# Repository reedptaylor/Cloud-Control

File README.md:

# Cloud-Control
Senior Capstone Project

## Abstract
Communicating with groups of people during an emergency situation is an extremely important and challenging task. The Cloud Control project aims to create a crowd control solution using a hexacopter drone. The project consists of a ground control application (GCS) which records the user and transmits their voice data to the drone. The drone is equipped with our custom chip and a speaker system which will amplify the voice messages to a target on the ground. The target application is to be able to fly the drone over a single person or a group of people and relay a message to them from the GCS through a microphone. The GCS sends the captured voice data to the chip on the drone over a wireless connection, and the chip processes the data and outputs it through the attached speaker. The potential applications of this project are very broad and include search and rescue operations, active shooter scenarios, and even recreational events like concerts and festivals.

## Devices
1. Raspberry Pi acts as the GCS. Sends data over NRF24 wireless module.
2. LPC 4088 acts as reciever and is connected to drone. Recieves data over NRF24 wireless module.
3. Android device can serve as remote to the GCS to control it and send audio (through a TCP connection to the GCS).

## Prerequisites
1. Install pyaudio on Raspberry Pi
2. Turn on SPI controls and install spidev on Raspberry Pi
3. Configure USB microphone thorugh `/etc/asound.conf` on Raspberry Pi

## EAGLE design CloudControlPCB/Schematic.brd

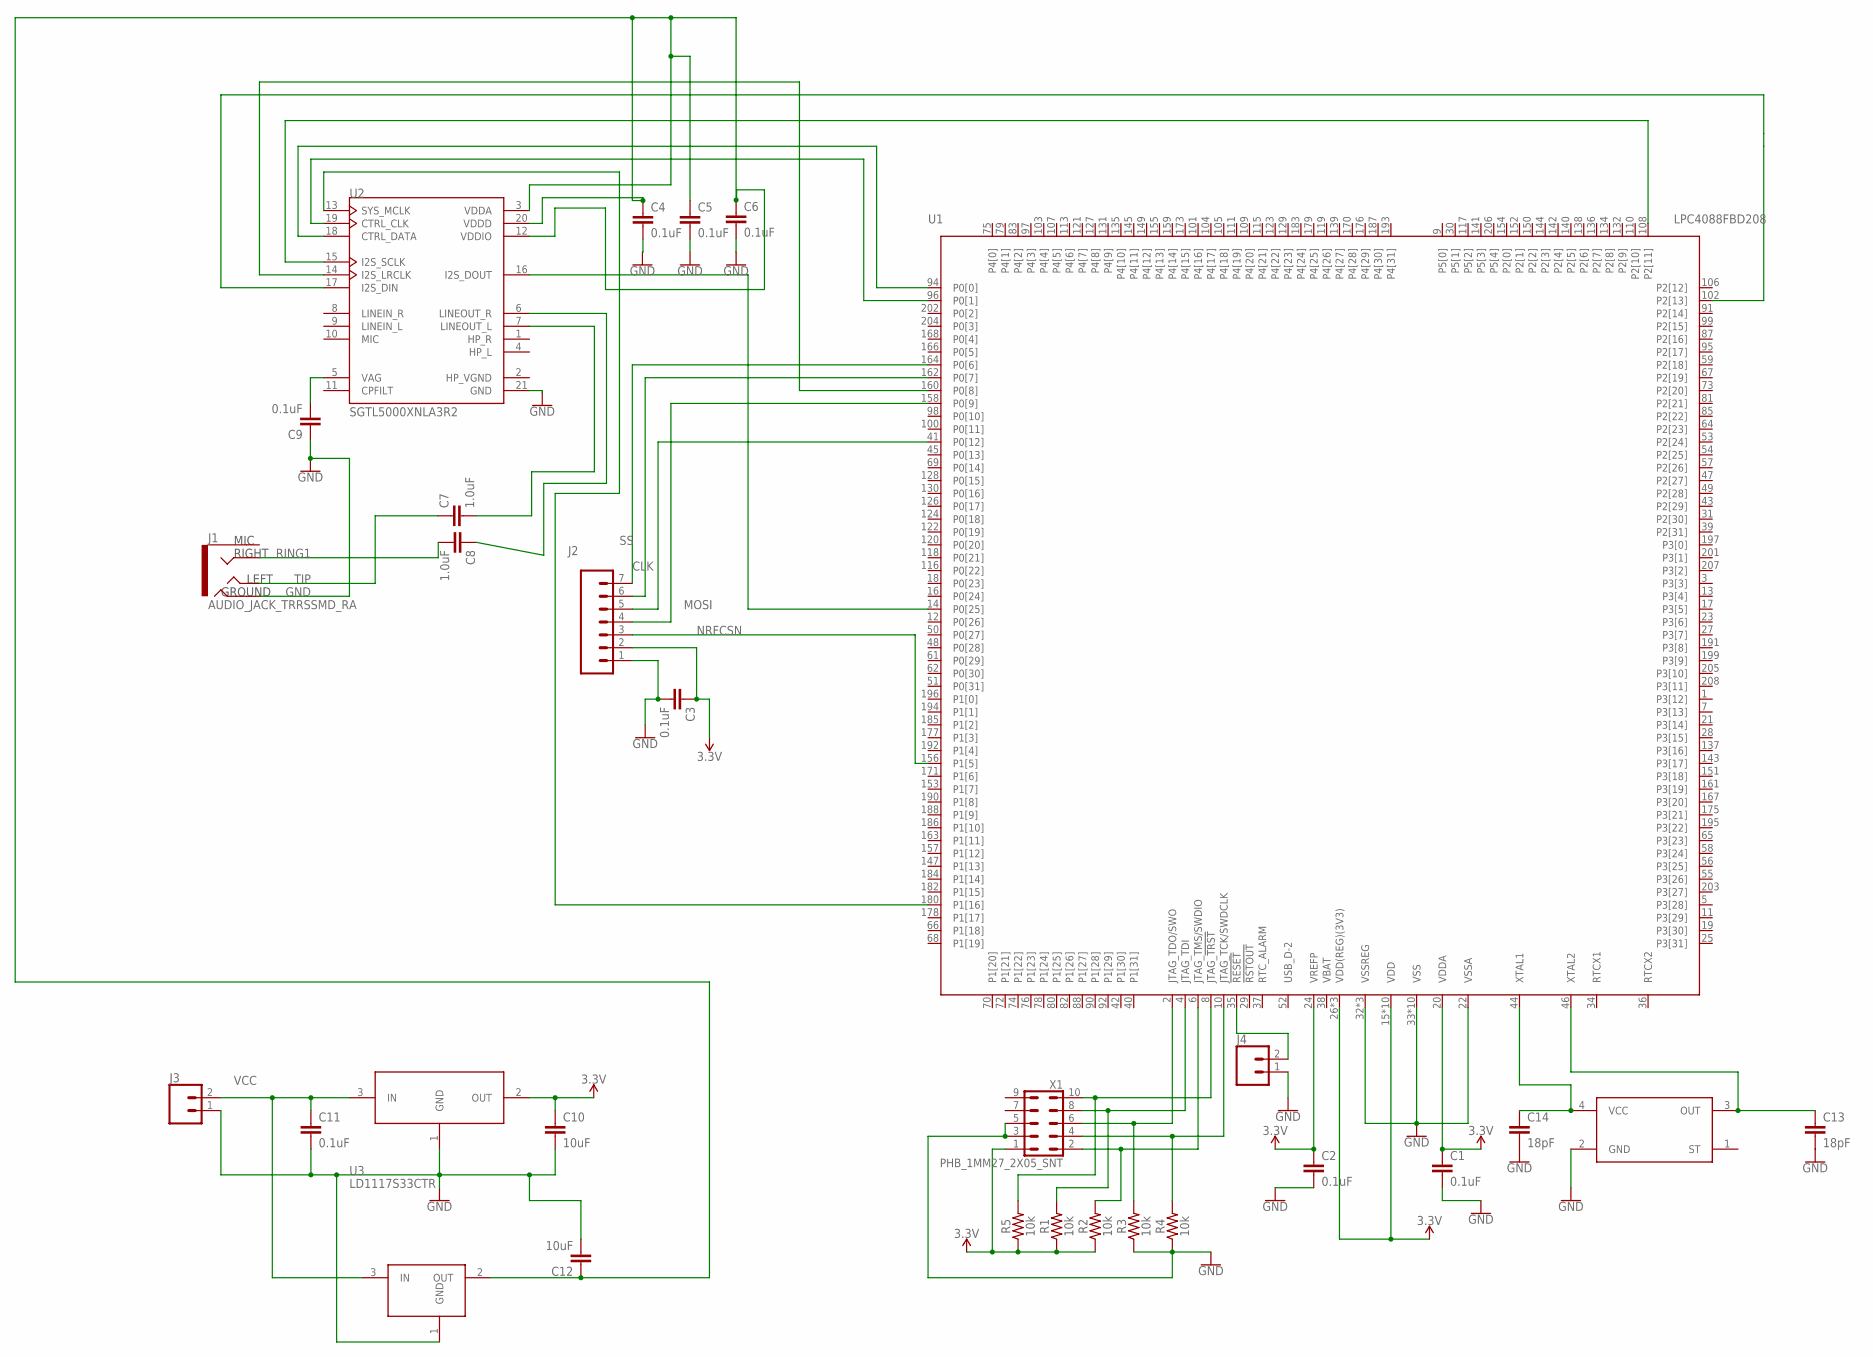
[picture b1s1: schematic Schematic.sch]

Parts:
C1, C2, C3, C11: 0.1uF; 0603
C4, C5, C6, C9: 0.1uF; 0402
C7, C8: 1.0uF; 0402
C10, C12: 10uF; 0603
C13, C14: 18pF; 0603
J1: AUDIO_JACK_TRRSSMD_RA; AUDIO_JACK_3.5MM_TRRS_SMD_RA
J2: CONN_07; 1X07
J3, J4: CONN_02; 1X02
R1, R2, R3, R4, R5: 10k; 0603
U1: LPC4088FBD208; SOT459-1
U2: SGTL5000XNLA3R2; QFN40P300X300X60-21N
U3: LD1117S33CTR; SOT223
U$1: SOT230P700X180-4N
U$2: XTAL_FA-238_25.0000MB-C3
X1: PHB_1MM27_2X05_SNT

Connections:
3.3V: C1.1, C2.1, C3.1, C10.1, J2.2, R1.1, R2.1, R5.1, U1.15 (VDD), U1.20 (VDDA), U1.24 (VREFP), U1.26 (VDD(REG)(3V3)), U1.60 (VDD), U1.71 (VDD), U1.86 (VDD(REG)(3V3)), U1.89 (VDD), U1.112 (VDD), U1.125 (VDD), U1.146 (VDD), U1.165 (VDD), U1.174 (VDD(REG)(3V3)), U1.181 (VDD), U1.198 (VDD), U3.2 (OUT), X1.1
CLK: J2.6, U1.162 (P0[7])
GND: C1.2, C2.2, C3.2, C4.2, C5.2, C6.2, C9.1, C10.2, C11.2, C12.2, C13.2, C14.2, J1.RING2, J2.1, J3.1, J4.1, R3.1, R4.1, U1.22 (VSSA), U1.32 (VSSREG), U1.33 (VSS), U1.63 (VSS), U1.77 (VSS), U1.84 (VSSREG), U1.93 (VSS), U1.114 (VSS), U1.133 (VSS), U1.148 (VSS), U1.169 (VSS), U1.172 (VSSREG), U1.189 (VSS), U1.200 (VSS), U2.21 (GND), U3.1 (GND), U$1.1 (GND), U$2.2 (GND), X1.3, X1.5; also elsewhere on the board
HP_VGND: U2.2 (HP_VGND)
MOSI: J2.4, U1.158 (P0[9])
unnamed: C8.1, U2.6 (LINEOUT_R)
unnamed: C7.2, U2.7 (LINEOUT_L)
unnamed: C14.1, U1.44 (XTAL1), U$2.4 (VCC)
unnamed: U1.14 (P0[25]), U2.16 (I2S_DOUT)
unnamed: U1.102 (P2[13]), U2.17 (I2S_DIN)
unnamed: U1.94 (P0[0]), U2.18 (CTRL_DATA)
unnamed: U1.96 (P0[1]), U2.19 (CTRL_CLK)
unnamed: U1.180 (P1[16]), U2.13 (SYS_MCLK)
unnamed: R3.2, U1.2 (JTAG_TDO/SWO), X1.6
unnamed: U1.108 (P2[11]), U2.15 (I2S_SCLK)
unnamed: U1.160 (P0[8]), U2.14 (I2S_LRCLK)
unnamed: R1.2, U1.4 (JTAG_TDI), X1.8
unnamed: R2.2, U1.6 (JTAG_TMS/SWDIO), X1.2
unnamed: R4.2, U1.10 (JTAG_TCK/SWDCLK), X1.4
unnamed: C9.2, U2.5 (VAG)
unnamed: R5.2, U1.8 (JTAG_!TRST), X1.10
unnamed: J2.5, U1.41 (P0[12])
unnamed: J4.2, U1.35 (!RESET!)
unnamed: C13.1, U1.46 (XTAL2), U$2.3 (OUT)
unnamed: C4.1, C5.1, C6.1, C12.1, U2.3 (VDDA), U2.12 (VDDIO), U2.20 (VDDD), U$1.2 (OUT)
NRFCSN: J2.3, U1.156 (P1[5])
RING1: C8.2, J1.RING1
SS: J2.7, U1.164 (P0[6])
TIP: C7.1, J1.TIP
VBAT: U1.38 (VBAT)
VCC: C11.1, J3.2, U3.3 (IN), U$1.3 (IN); also elsewhere on the board

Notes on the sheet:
MIC
RIGHT
LEFT
GROUND

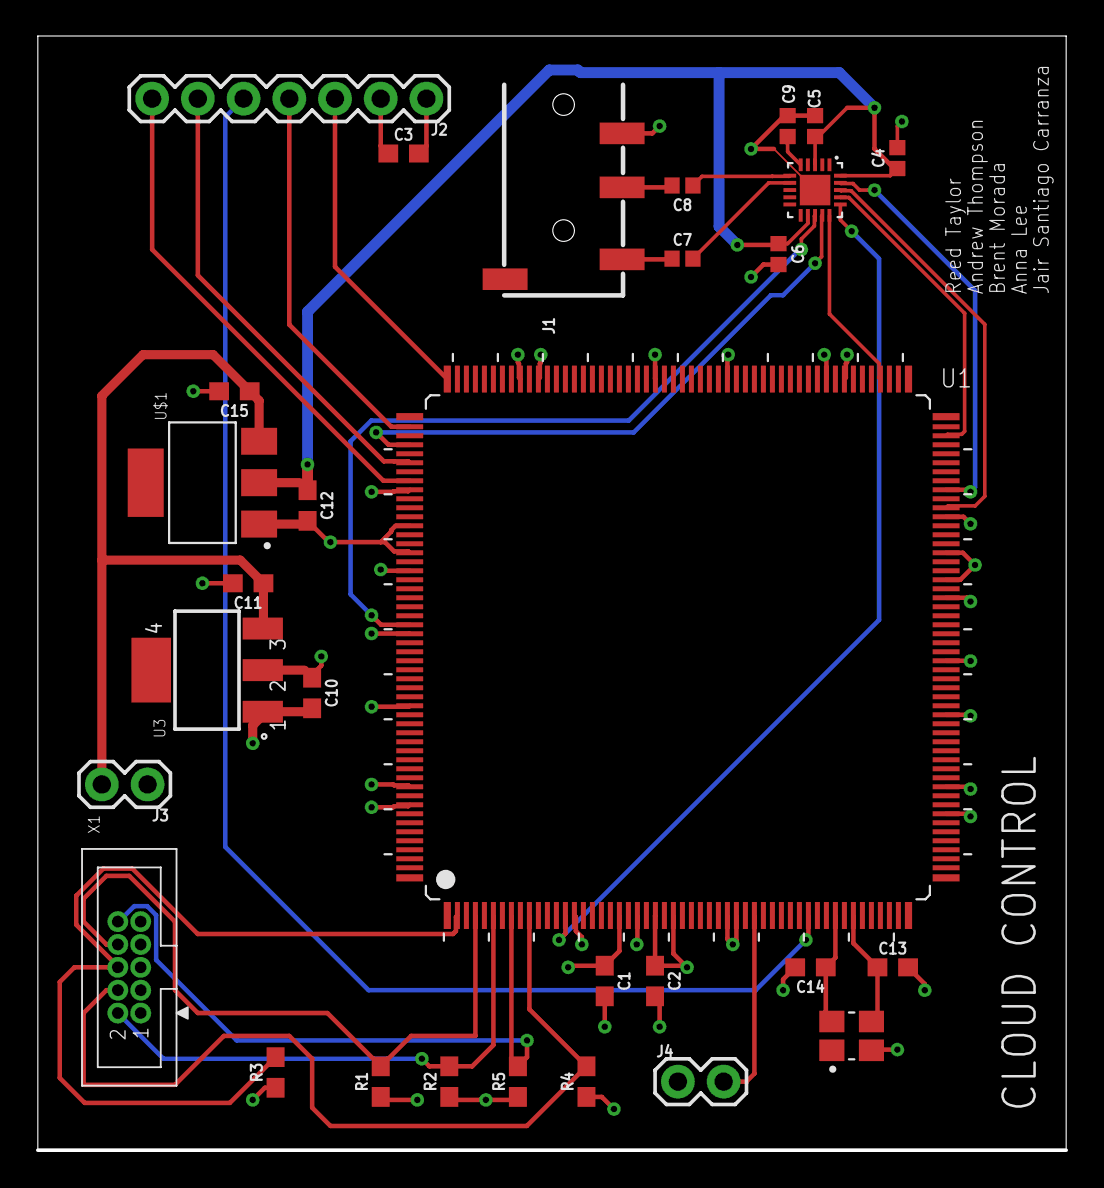
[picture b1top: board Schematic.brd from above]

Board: 4 copper layers, 57.1 x 61.9 mm, 30 parts (0 on the bottom side), 29 nets.

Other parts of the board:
C15: 0.1uF; 0603

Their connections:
GND: C15.2; also elsewhere on the board
VCC: C15.1; also elsewhere on the board

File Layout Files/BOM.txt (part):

Partlist exported from /Users/reed/Desktop/Cloud-Control/CloudControlPCB/Schematic.sch at 12/12/18 3:36 PM

Part Value                    Device                    Package                      Description                                                                                                     AVAILABILITY DESCRIPTION                                                                                   MF                 MP              PACKAGE                        PRICE PROD_ID    SF_ID     VALUE
C1   0.1uF                    0.1UF-0603-25V-(+80/-20%) 0603                         0.1µF ceramic capacitors                                                                                                                                                                                                                                                                           CAP-00810            0.1uF
C2   0.1uF                    0.1UF-0603-25V-(+80/-20%) 0603                         0.1µF ceramic capacitors                                                                                                                                                                                                                                                                           CAP-00810            0.1uF
C3   0.1uF                    0.1UF-0603-25V-(+80/-20%) 0603                         0.1µF ceramic capacitors                                                                                                                                                                                                                                                                           CAP-00810            0.1uF
C4   0.1uF                    0.1UF-0402-16V-10%        0402                         0.1µF ceramic capacitors                                                                                                                                                                                                                                                                           CAP-12416            0.1uF
C5   0.1uF                    0.1UF-0402-16V-10%        0402                         0.1µF ceramic capacitors                                                                                                                                                                                                                                                                           CAP-12416            0.1uF
C6   0.1uF                    0.1UF-0402-16V-10%        0402                         0.1µF ceramic capacitors                                                                                                                                                                                                                                                                           CAP-12416            0.1uF
C7   1.0uF                    1.0UF-0402-16V-10%        0402                         1µF ceramic capacitors                                                                                                                                                                                                                                                                             CAP-12417            1.0uF
C8   1.0uF                    1.0UF-0402-16V-10%        0402                         1µF ceramic capacitors                                                                                                                                                                                                                                                                             CAP-12417            1.0uF
C9   0.1uF                    0.1UF-0402-16V-10%        0402                         0.1µF ceramic capacitors                                                                                                                                                                                                                                                                           CAP-12416            0.1uF
C10  10uF                     10UF-0603-6.3V-20%        0603                         10.0µF ceramic capacitors                                                                                                                                                                                                                                                                          CAP-11015            10uF 
C11  0.1uF                    0.1UF-0603-25V-(+80/-20%) 0603                         0.1µF ceramic capacitors                                                                                                                                                                                                                                                                           CAP-00810            0.1uF
C12  10uF                     10UF-0603-6.3V-20%        0603                         10.0µF ceramic capacitors                                                                                                                                                                                                                                                                          CAP-11015            10uF 
C13  18pF                     18PF-0603-50V-5%          0603                         18pF ceramic capacitors                                                                                                                                                                                                                                                                            CAP-08267            18pF 
C14  18pF                     18PF-0603-50V-5%          0603                         18pF ceramic capacitors                                                                                                                                                                                                                                                                            CAP-08267            18pF 
C15  0.1uF                    0.1UF-0603-25V-(+80/-20%) 0603                         0.1µF ceramic capacitors                                                                                                                                                                                                                                                                           CAP-00810            0.1uF
J1   AUDIO_JACK_TRRSSMD_RA    AUDIO_JACK_TRRSSMD_RA     AUDIO_JACK_3.5MM_TRRS_SMD_RA Audio Jack - 3.5mm TRRS (SMD)                                                                                                                                                                                                                                                                      CONN-10676 PRT-12639      
J2                            CONN_07                   1X07                         Multi connection point. Often used as Generic Header-pin footprint for 0.1 inch spaced/style header connections                                                                                                                                                                                                              
J3                            CONN_02                   1X02                         Multi connection point. Often used as Generic Header-pin footprint for 0.1 inch spaced/style header connections                                                                                                                                                                                                              
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
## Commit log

2018-11-06 Create C audio stream files
2018-11-06 Added portaudio library, portaudio test, and began server implementation
2018-11-06 Fixed README
2018-11-06 added client code, began impl. audio sent over tcp, not yet working.
2018-11-07 More work on audio stream, should be close to working.
2018-11-07 Send individual samples, data is through but played at wrong rate
2018-11-07 audio streaming (not live) is now working
2018-11-10 Started trying to implment real time in client1 and server1
2018-11-14 Refactor directory structure and file naming
2018-11-14 initial push for PCB
2018-11-16 added power and SPI connector to schematic
2018-11-17 added audio codec to schematic
2018-11-19 added more connections
2018-11-20 Added connections to DAC for I2S
2018-11-20 Adjusted Vref and Vdda to have bypass capacitors
2018-11-26 Create uda1380.c
    need to edit for SGTL5000
2018-11-26 added more wireing
2018-11-28 Added codec capacitors into schematic, can't do much else without the amplifier module.
2018-11-28 fixed headphone jack
2018-11-30 Fixed some wiring on the DAC
2018-12-01 Fixed DAC Wiring
2018-12-03 Add small regulator circuit (Hopefully no merging issues)
2018-12-05 add 2-pin jumper for powersupply and 3.3v regulator
2018-12-05 Change 100pF cap to 0402 package size for regulator circuit
2018-12-05 Finalize schematic
2018-12-06 Generated and started layout
2018-12-06 made progress on layout
2018-12-06 Fixed 1.8V regulator connections
2018-12-06 Connected Crystal on layout
2018-12-07 added more routes
2018-12-07 More routing on layout
2018-12-08 finished routing
2018-12-11 up to date 12/11
2018-12-11 finished all layout and added gerber files
2019-01-16 updated layout files
2019-01-16 added audio playback functionality on LPC
2019-01-23 added ethernet file
2019-01-23 ethernet combination
2019-01-30 Update python chunk size
2019-01-30 small python streaming changes
2019-01-30 added skeleton for sending over nrf
2019-02-04 Removed examples/unnecessary files
2019-02-04 removed prev file, added SGTL5000 header def file
    still need to add initialization/interface files, additional library files
2019-02-06 Fixed a value
2019-02-06 Updated header for codec driver
2019-02-06 Fixed file name and path
2019-02-06 Fixed typo, cleaned up indenting
2019-02-06 Added UDA1280.c for reference
2019-02-06 Added UDA1380.h for reference
2019-02-06 Added board.h
    from LPC Open
2019-02-06 DRV_SGTL_5000.c is a CMSIS Template for now
2019-02-06 fixed minor thing
2019-02-06 file name fix
2019-02-13 Initial commit of NRF24 driver
2019-02-13 Updated sendsound.py with debugging help
2019-02-13 test main for recv'ing data
2019-02-20 add nrf python file
2019-02-21 fixed JTAG on PCB
2019-02-21 fixed framerate
2019-02-22 added basic read/write function defs
    init function will need to be edited
2019-02-27 updated codec driver.h file
2019-02-27 updated codec driver .h file
    added 4 default reg values
2019-02-27 updated codec driver .c
    need to check some addresses
2019-02-27 Deleted board.h
2019-02-27 uploaded some includes
    chip.h
    chip_lpc407x_8x.h
    lpc_types.h
    sys_config.h
2019-02-27 more uploads
2019-02-27 renamed NRFCSN to CE
2019-03-02 Updated codec driver
2019-03-04 Cleaned up Repo and added our streaming files
2019-03-06 Initial PCBA Support changes
2019-04-01 changed UI
2019-04-01 updated schematic
2019-04-10 update with i2c address
2019-04-10 Only need to define i2c bus now
2019-04-15 Added preliminary poster
2019-04-16 Continued updating poster
2019-04-17 Continue updating poster
2019-04-24 updated RPi UI
2019-04-29 Use internal clocking, new NRF code and settings for 2nd PCB
2019-04-29 created separate PCB and dev versions
2019-04-29 Added UI Screenshot to poster
2019-05-01 Added base of android app
2019-05-06 Added CloudControl Remote functionality (without audio sending)
2019-05-06 Minor changes and code clean up
2019-05-06 Refined poster
2019-05-08 Added audio capability to android tablet
2019-05-08 added logo change
2019-05-08 fixed logo
2019-05-08 Updated poster
2019-05-14 NRF24 fix. thats it. thats literally it
2019-05-15 Updated UI and poster
2019-05-18 Refine poster
2019-05-19 demo file
2019-05-20 FINAL POSTER
2019-05-21 deleted original file
2019-05-21 Replaced old files with updated drivers
    .c not complete
2019-05-21 deleted old file
2019-05-21 uploaded updated drivers
    .c not finished yet
2019-05-21 updatee
2019-05-21 updated i2c driver for sgtl5000
    will add includes later
2019-05-21 wrote modify function
2019-05-24 nrf24 for teensyduino
2019-05-25 added arduino capability
2019-05-28 fixed arduino code - sample rate set to 11025
2019-05-30 changed sample rate to support arduino

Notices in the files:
parts and their libraries:
SparkFun-Capacitors: Licensing: Creative Commons ShareAlike 4.0 International - https://creativecommons.org/licenses/by-sa/4.0
